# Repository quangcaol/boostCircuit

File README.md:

# 3.7V/4.2V To 5V 1A BOOST CONVERTER
Schematic and PCB layout of boost circuit using ADP1613 switching voltage regulator. Designed with KiCad
PCB layout is constrained by PCB layout which is included in ADP1613 DATASHEET by the Manufacturer

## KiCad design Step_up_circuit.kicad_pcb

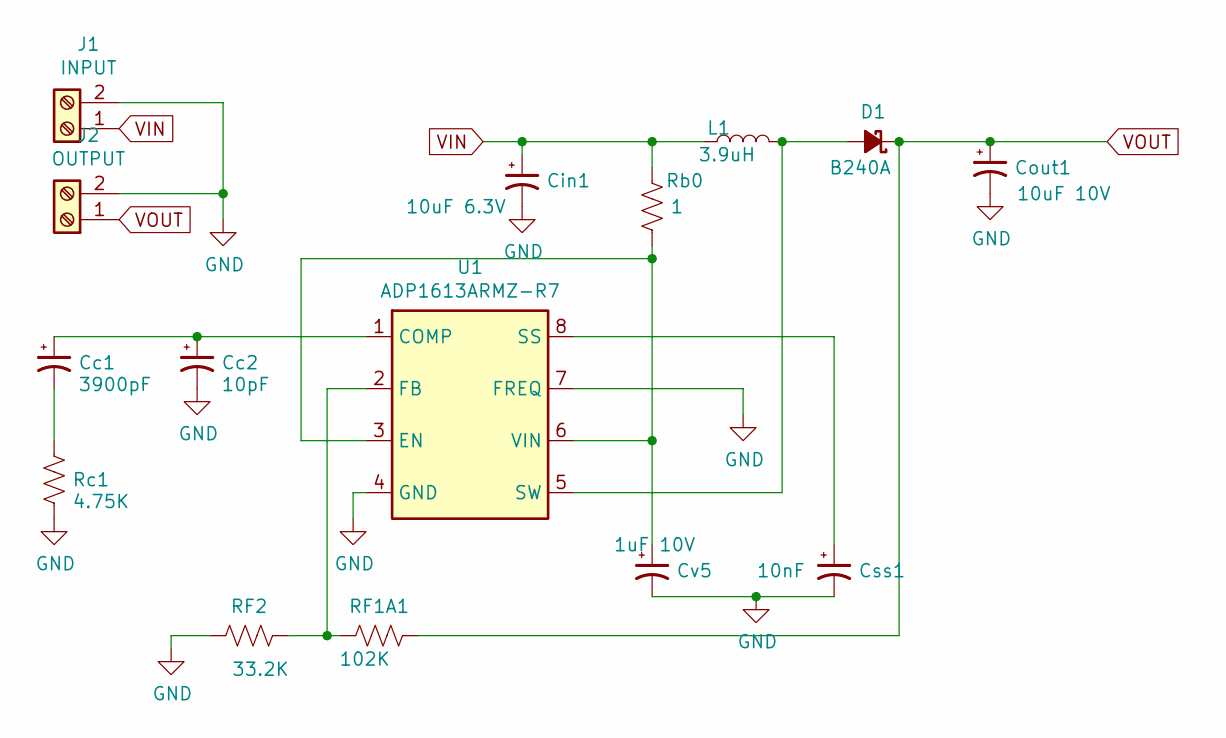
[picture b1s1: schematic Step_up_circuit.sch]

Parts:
Cc1: 3900pF; C_01005_0402Metric
Cc2: 10pF; C_01005_0402Metric
Cin1: 10uF 6.3V; C_1206_3216Metric
Cout1: 10uF 10V; C_0805_2012Metric
Css1: 10nF; C_0402_1005Metric
Cv5: 1uF 10V; C_0603_1608Metric
D1: B240A; D_SMA
J1: INPUT; TerminalBlock_Altech_AK300-2_P5.00mm
J2: OUTPUT; TerminalBlock_Altech_AK300-2_P5.00mm
L1: 3.9uH; L_Bourns-SRN4018
RF1A1: 102K; R_01005_0402Metric
RF2: 33.2K; R_01005_0402Metric
Rb0: 1; R_01005_0402Metric
Rc1: 4.75K; R_01005_0402Metric
U1: ADP1613ARMZ-R7; MSOP-8_3x3mm_P0.65mm

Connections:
GND: Cc2.2, Cin1.2, Cout1.2, Css1.2, Cv5.2, J1.2, J2.2, RF2.1, Rc1.2, U1.4 (GND), U1.7 (FREQ)
unnamed: Cc1.1, Cc2.1, U1.1 (COMP)
unnamed: Cc1.2, Rc1.1
unnamed: Css1.1, U1.8 (SS)
unnamed: Cv5.1, Rb0.1, U1.3 (EN), U1.6 (VIN)
unnamed: D1.2 (A), L1.2, U1.5 (SW)
unnamed: RF1A1.1, RF2.2, U1.2 (FB)
VIN: Cin1.1, J1.1, L1.1, Rb0.2
VOUT: Cout1.1, D1.1 (K), J2.1, RF1A1.2

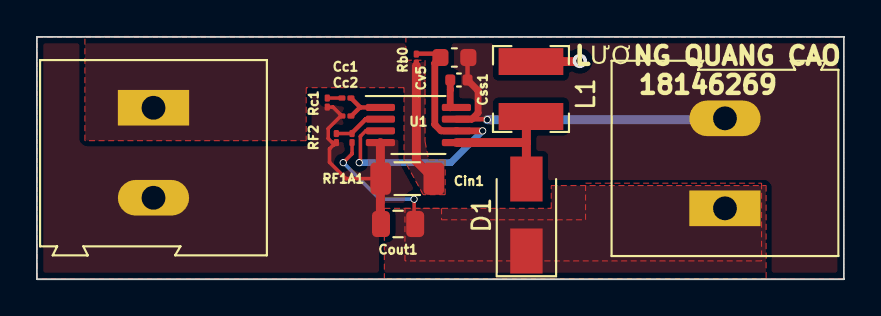
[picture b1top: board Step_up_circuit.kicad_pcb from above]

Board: 2 copper layers, 44.8 x 13.5 mm, 15 parts (0 on the bottom side), 9 nets.

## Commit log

2021-01-04 Main file
